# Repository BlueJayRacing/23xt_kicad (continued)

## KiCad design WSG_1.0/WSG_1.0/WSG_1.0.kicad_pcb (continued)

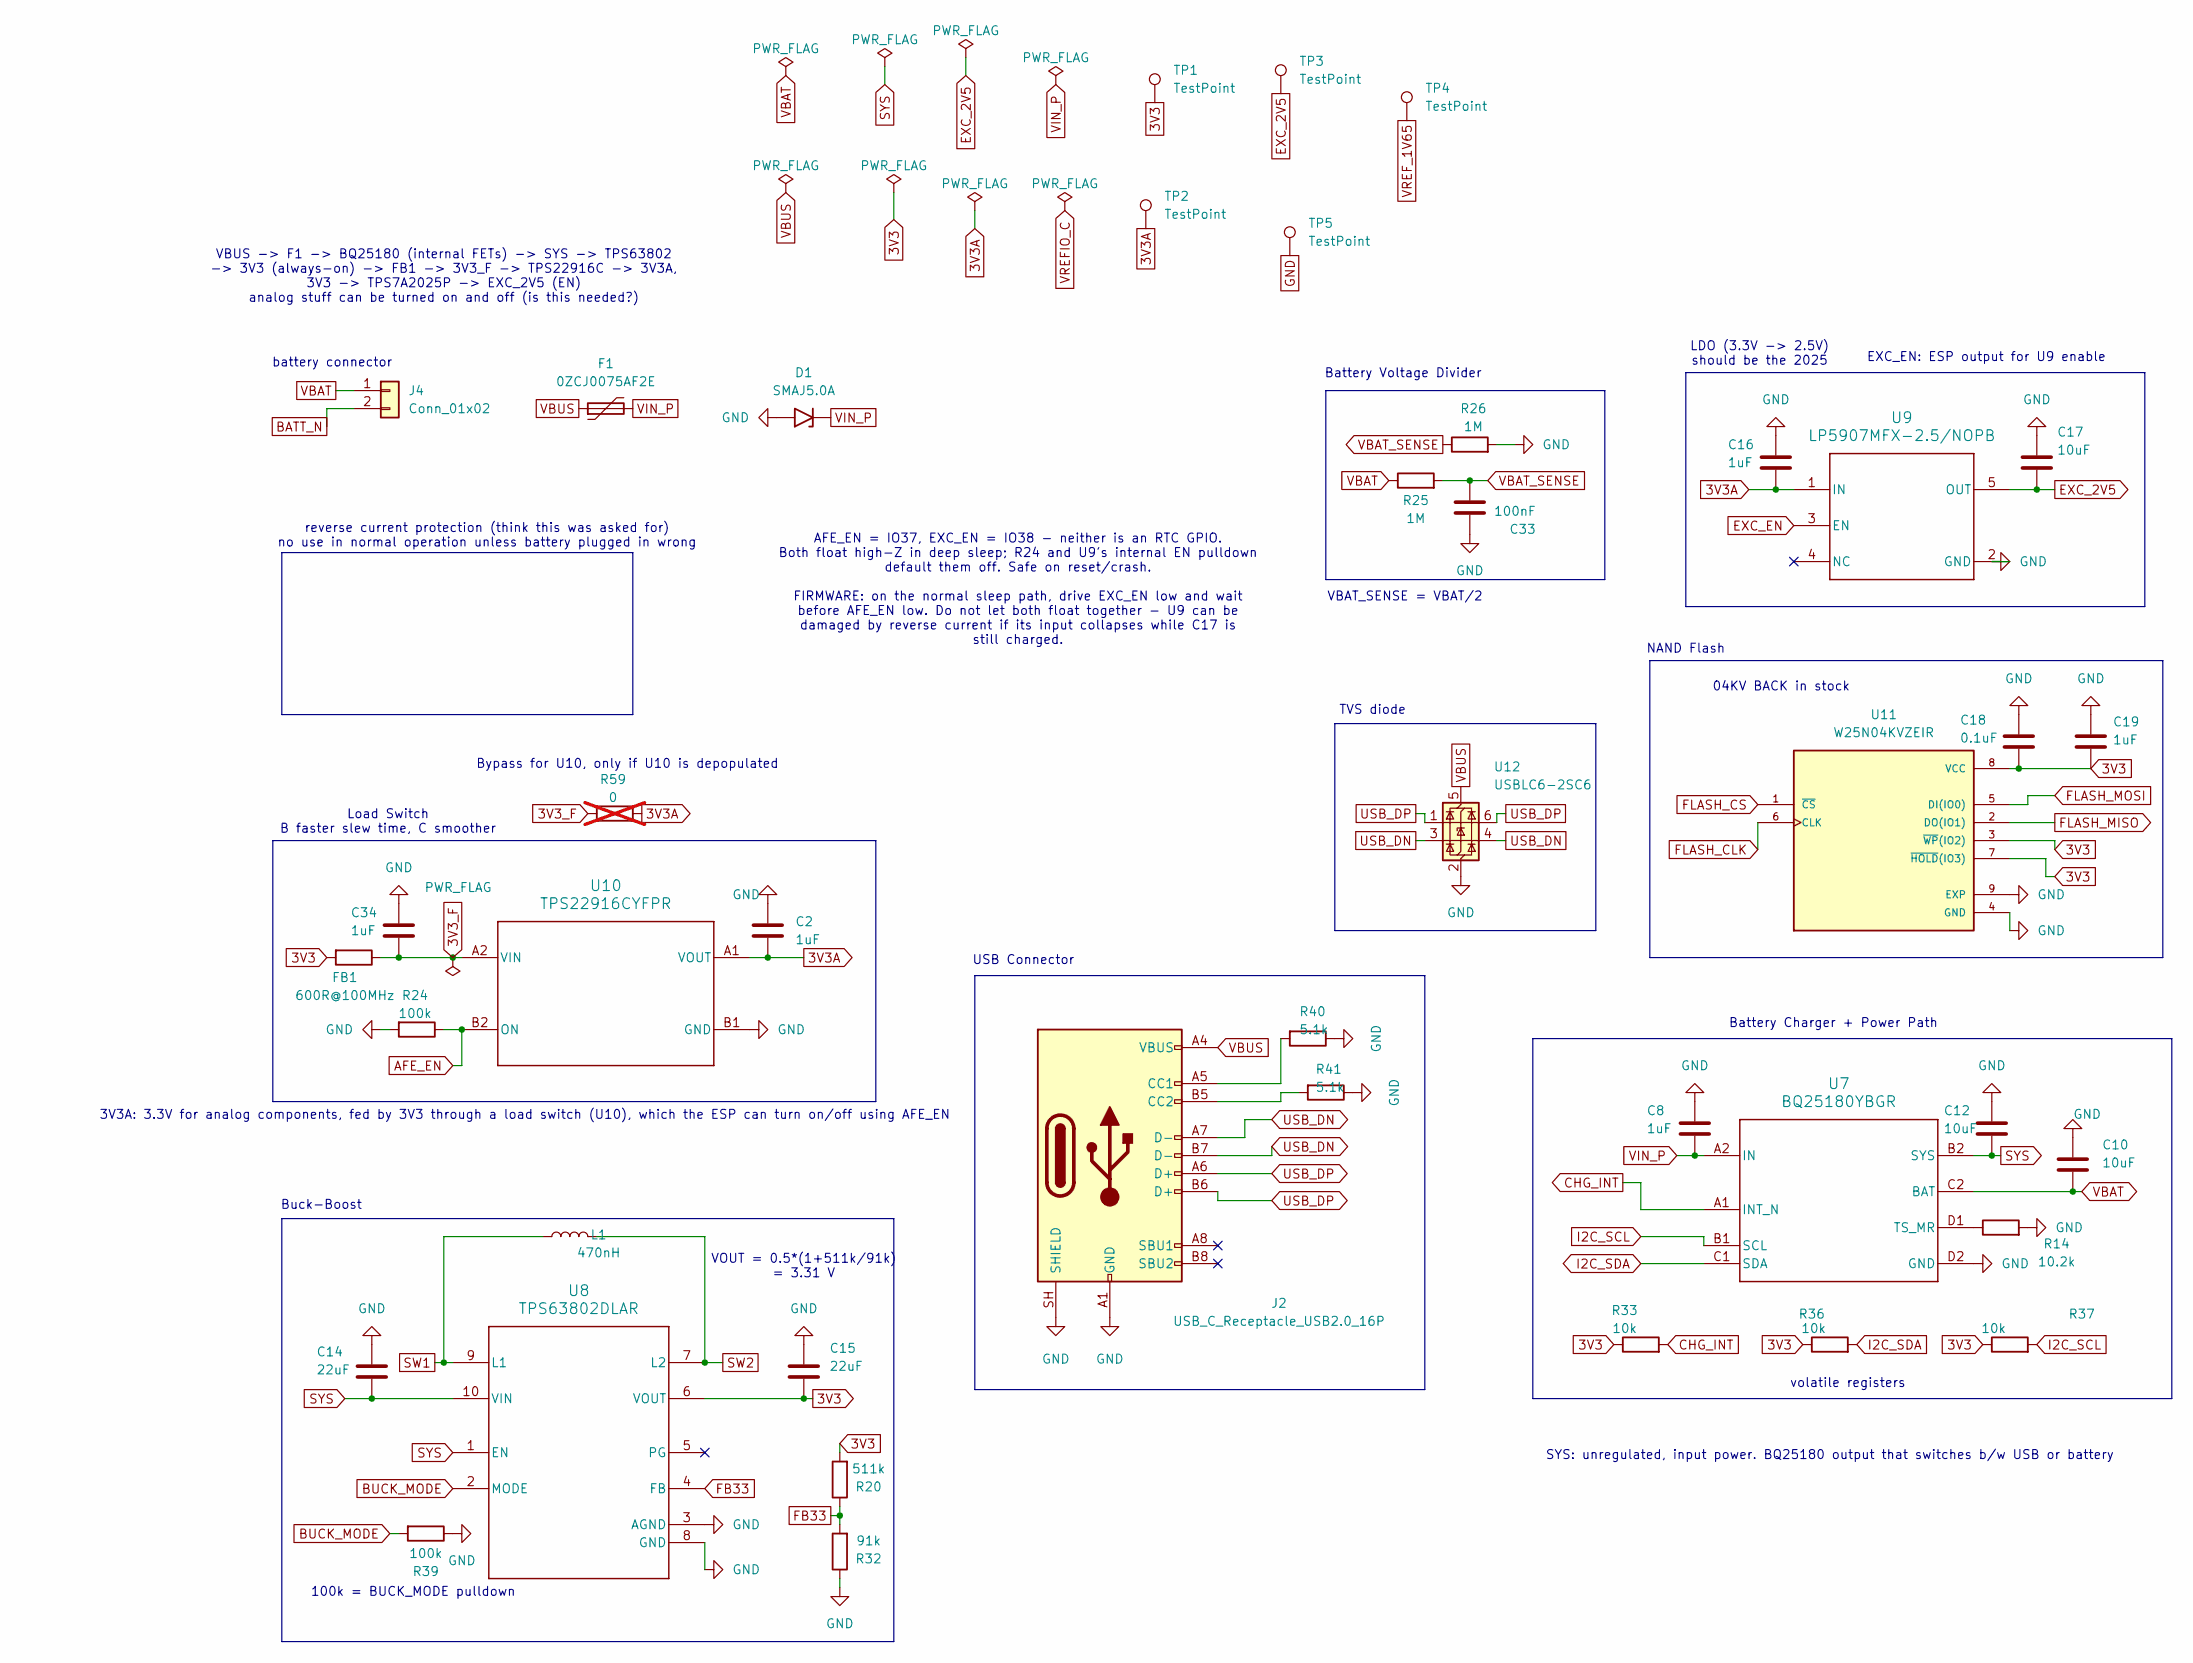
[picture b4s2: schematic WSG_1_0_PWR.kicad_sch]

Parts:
C2, C8, C16, C19, C34: 1uF; C_0402_1005Metric_Pad0.74x0.62mm_HandSolder
C10, C12: 10uF; C_0402_1005Metric_Pad0.74x0.62mm_HandSolder
C14, C15: 22uF; C_0603_1608Metric_Pad1.08x0.95mm_HandSolder; MPN CL10A226MQ8NRNE
C17: 10uF; C_0603_1608Metric_Pad1.08x0.95mm_HandSolder; MPN GRM188R60J106ME84
C18: 0.1uF; C_0402_1005Metric_Pad0.74x0.62mm_HandSolder
C33: 100nF; C_0402_1005Metric_Pad0.74x0.62mm_HandSolder
D1: SMAJ5.0A; D_SMA
F1: 0ZCJ0075AF2E; Fuse_1206_3216Metric
FB1: 600R@100MHz; L_0402_1005Metric; MPN BLM15AG601SN1D
J2: USB_C_Receptacle_USB2.0_16P; USB_C_Receptacle_GCT_USB4110; MPN USB4110-GF-A
J4: Conn_01x02; JST_S2B-PH-K-S_LF__SN_-2pin_male
L1: 470nH; L_Coilcraft_XxL4020; MPN XGL4020-471MEC
R14: 10.2k; R_0402_1005Metric_Pad0.72x0.64mm_HandSolder
R20: 511k; R_0402_1005Metric_Pad0.72x0.64mm_HandSolder
R24, R39: 100k; R_0402_1005Metric_Pad0.72x0.64mm_HandSolder
R25, R26: 1M; R_0402_1005Metric_Pad0.72x0.64mm_HandSolder
R32: 91k; R_0402_1005Metric_Pad0.72x0.64mm_HandSolder
R33, R36, R37: 10k; R_0402_1005Metric_Pad0.72x0.64mm_HandSolder
R40, R41: 5.1k; R_0402_1005Metric_Pad0.72x0.64mm_HandSolder
R59: 0; R_0402_1005Metric_Pad0.72x0.64mm_HandSolder; not fitted
TP1, TP2, TP3, TP4, TP5: TestPoint; TestPoint_Pad_1.0x1.0mm
U7: BQ25180YBGR; IC_BQ25180YBGR
U8: TPS63802DLAR; DLA0010A
U9: LP5907MFX-2.5/NOPB; SOT-23-5
U10: TPS22916CYFPR; IC_TPS22916BYFPR
U11: W25N04KVZEIR; IC_W25N04KVZEIR; PARTREV I
U12: USBLC6-2SC6; SOT-23-6

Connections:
3V3: C15.2, C18.2, C19.2, FB1.2, R20.2, R33.1, R36.1, R37.1, TP1.1 (1_1), U8.6 (VOUT), U11.3 (~WP(IO2)), U11.7 (~HOLD(IO3)), U11.8 (VCC); also elsewhere on the board
3V3A: C2.2, C16.2, R59.1, TP2.1 (1_1), U9.1 (IN), U10.A1 (VOUT); also elsewhere on the board
3V3_F: C34.2, FB1.1, R59.2, U10.A2 (VIN)
AFE_EN: R24.1, U10.B2 (ON); also elsewhere on the board
BATT_N: J4.2; also elsewhere on the board
BUCK_MODE: R39.2, U8.2 (MODE); also elsewhere on the board
CHG_INT: R33.2, U7.A1 (INT_N); also elsewhere on the board
EXC_2V5: C17.2, TP3.1 (1_1), U9.5 (OUT); also elsewhere on the board
EXC_EN: U9.3 (EN); also elsewhere on the board
FB33: R20.1, R32.2, U8.4 (FB)
FLASH_CLK: U11.6 (CLK); also elsewhere on the board
FLASH_CS: U11.1 (~CS); also elsewhere on the board
FLASH_MISO: U11.2 (DO(IO1)); also elsewhere on the board
FLASH_MOSI: U11.5 (DI(IO0)); also elsewhere on the board
GND: C2.1, C8.1, C10.1, C12.1, C14.1, C15.1, C16.1, C17.1, C18.1, C19.1, C33.2, C34.1, D1.2 (A2), J2.A1 (GND), J2.A12 (GND), J2.B1 (GND), J2.B12 (GND), J2.SH (SHIELD), R14.2, R24.2, R26.2, R32.1, R39.1, R40.1, R41.1, TP5.1 (1_1), U7.D2 (GND), U8.3 (AGND), U8.8 (GND), U9.2 (GND), U10.B1 (GND), U11.4 (GND), U11.9 (EXP), U12.2 (GND); also elsewhere on the board
I2C_SCL: R37.2, U7.B1 (SCL); also elsewhere on the board
I2C_SDA: R36.2, U7.C1 (SDA); also elsewhere on the board
unnamed: J2.A5 (CC1), R40.2
unnamed: J2.B5 (CC2), R41.2
unnamed: R14.1, U7.D1 (TS_MR)
SW1: L1.1, U8.9 (L1)
SW2: L1.2, U8.7 (L2)
SYS: C12.2, C14.2, U7.B2 (SYS), U8.1 (EN), U8.10 (VIN)
USB_DN: J2.A7 (D-), J2.B7 (D-), U12.3 (I/O2), U12.4 (I/O2); also elsewhere on the board
USB_DP: J2.A6 (D+), J2.B6 (D+), U12.1 (I/O1), U12.6 (I/O1); also elsewhere on the board
VBAT: C10.2, J4.1, R25.1, U7.C2 (BAT)
VBAT_SENSE: C33.1, R25.2, R26.1; also elsewhere on the board
VBUS: F1.1, J2.A4 (VBUS), J2.A9 (VBUS), J2.B4 (VBUS), J2.B9 (VBUS), U12.5 (VBUS)
VIN_P: C8.2, D1.1 (A1), F1.2, U7.A2 (IN)
VREF_1V65: TP4.1 (1_1); also elsewhere on the board

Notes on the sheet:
3V3A: 3.3V for analog components, fed by 3V3 through a load switch (U10), which the ESP can turn on/off using AFE_EN
100k = BUCK_MODE pulldown
LDO (3.3V -> 2.5V) should be the 2025
04KV BACK in stock
Battery Voltage Divider
NAND Flash
VBAT_SENSE = VBAT/2
volatile registers
EXC_EN: ESP output for U9 enable
Load Switch B faster slew time, C smoother
Battery Charger + Power Path
VBUS -> F1 -> BQ25180 (internal FETs) -> SYS -> TPS63802 -> 3V3 (always-on) -> FB1 -> 3V3_F -> TPS22916C -> 3V3A, 3V3 -> TPS7A2025P -> EXC_2V5 (EN) analog stuff can be turned on and off (is this needed?)
AFE_EN = IO37, EXC_EN = IO38 - neither is an RTC GPIO. Both float high-Z in deep sleep; R24 and U9's internal EN pulldown default them off. Safe on reset/crash. FIRMWARE: on the normal sleep path, drive EXC_EN low and wait before AFE_EN low. Do not let both float together - U9 can be damaged by rev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
Buck-Boost
USB Connector
battery connector
reverse current protection (think this was asked for) no use in normal operation unless battery plugged in wrong
SYS: unregulated, input power. BQ25180 output that switches b/w USB or battery
TVS diode
Bypass for U10, only if U10 is depopulated
VOUT = 0.5*(1+511k/91k) = 3.31 V

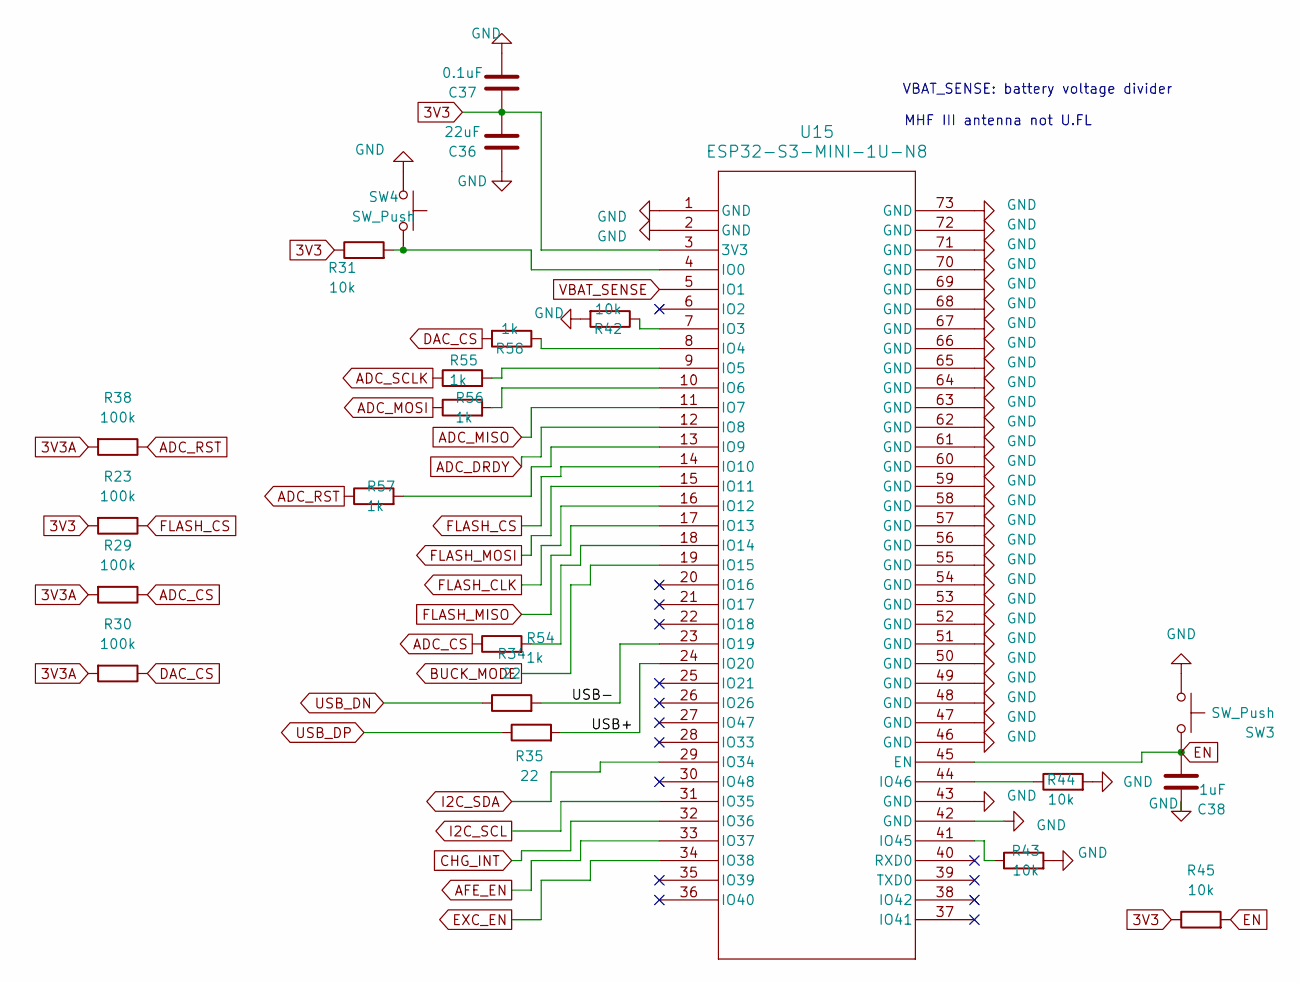
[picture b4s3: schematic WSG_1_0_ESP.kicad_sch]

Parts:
C36: 22uF; C_0603_1608Metric_Pad1.08x0.95mm_HandSolder; MPN CL10A226MQ8NRNE
C37: 0.1uF; C_0402_1005Metric_Pad0.74x0.62mm_HandSolder
C38: 1uF; C_0402_1005Metric_Pad0.74x0.62mm_HandSolder
R23, R29, R30, R38: 100k; R_0402_1005Metric_Pad0.72x0.64mm_HandSolder
R31, R42, R43, R44, R45: 10k; R_0402_1005Metric_Pad0.72x0.64mm_HandSolder
R34, R35: 22; R_0402_1005Metric_Pad0.72x0.64mm_HandSolder
R54, R55, R56, R57, R58: 1k; R_0402_1005Metric_Pad0.72x0.64mm_HandSolder
SW3, SW4: SW_Push; NANOT100AS_butt
U15: ESP32-S3-MINI-1U-N8; ESP32-S3-MINI-1U_EXP

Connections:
3V3: C36.1, C37.1, R23.2, R31.1, R45.1, U15.3 (3V3); also elsewhere on the board
3V3A: R29.2, R30.2, R38.2; also elsewhere on the board
/WSG_ESP/USB+: R35.2, U15.24 (IO20)
/WSG_ESP/USB-: R34.2, U15.23 (IO19)
ADC_CS: R29.1, R54.1; also elsewhere on the board
ADC_DRDY: U15.12 (IO8); also elsewhere on the board
ADC_MISO: U15.11 (IO7); also elsewhere on the board
ADC_MOSI: R56.1; also elsewhere on the board
ADC_RST: R38.1, R57.1; also elsewhere on the board
ADC_SCLK: R55.1; also elsewhere on the board
AFE_EN: U15.33 (IO37); also elsewhere on the board
BUCK_MODE: U15.19 (IO15); also elsewhere on the board
CHG_INT: U15.32 (IO36); also elsewhere on the board
DAC_CS: R30.1, R58.2; also elsewhere on the board
EN: C38.2, R45.2, SW3.2, U15.45 (EN)
EXC_EN: U15.34 (IO38); also elsewhere on the board
FLASH_CLK: U15.16 (IO12); also elsewhere on the board
FLASH_CS: R23.1, U15.14 (IO10); also elsewhere on the board
FLASH_MISO: U15.17 (IO13); also elsewhere on the board
FLASH_MOSI: U15.15 (IO11); also elsewhere on the board
GND: C36.2, C37.2, C38.1, R42.2, R43.2, R44.2, SW3.1, SW4.1, U15.1 (GND), U15.2 (GND), U15.42 (GND), U15.43 (GND), U15.46 (GND), U15.47 (GND), U15.48 (GND), U15.49 (GND), U15.50 (GND), U15.51 (GND), U15.52 (GND), U15.53 (GND), U15.54 (GND), U15.55 (GND), U15.56 (GND), U15.57 (GND), U15.58 (GND), U15.59 (GND), U15.60 (GND), U15.61 (GND), U15.62 (GND), U15.63 (GND), U15.64 (GND), U15.65 (GND), U15.66 (GND), U15.67 (GND), U15.68 (GND), U15.69 (GND), U15.70 (GND), U15.71 (GND), U15.72 (GND), U15.73 (GND); also elsewhere on the board
I2C_SCL: U15.31 (IO35); also elsewhere on the board
I2C_SDA: U15.29 (IO34); also elsewhere on the board
unnamed: R31.2, SW4.2, U15.4 (IO0)
unnamed: R42.1, U15.7 (IO3)
unnamed: R58.1, U15.8 (IO4)
unnamed: R55.2, U15.9 (IO5)
unnamed: R56.2, U15.10 (IO6)
unnamed: R57.2, U15.13 (IO9)
unnamed: R54.2, U15.18 (IO14)
unnamed: R43.1, U15.41 (IO45)
unnamed: R44.1, U15.44 (IO46)
USB_DN: R34.1; also elsewhere on the board
USB_DP: R35.1; also elsewhere on the board
VBAT_SENSE: U15.5 (IO1); also elsewhere on the board

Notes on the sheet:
MHF III antenna not U.FL
VBAT_SENSE: battery voltage divider

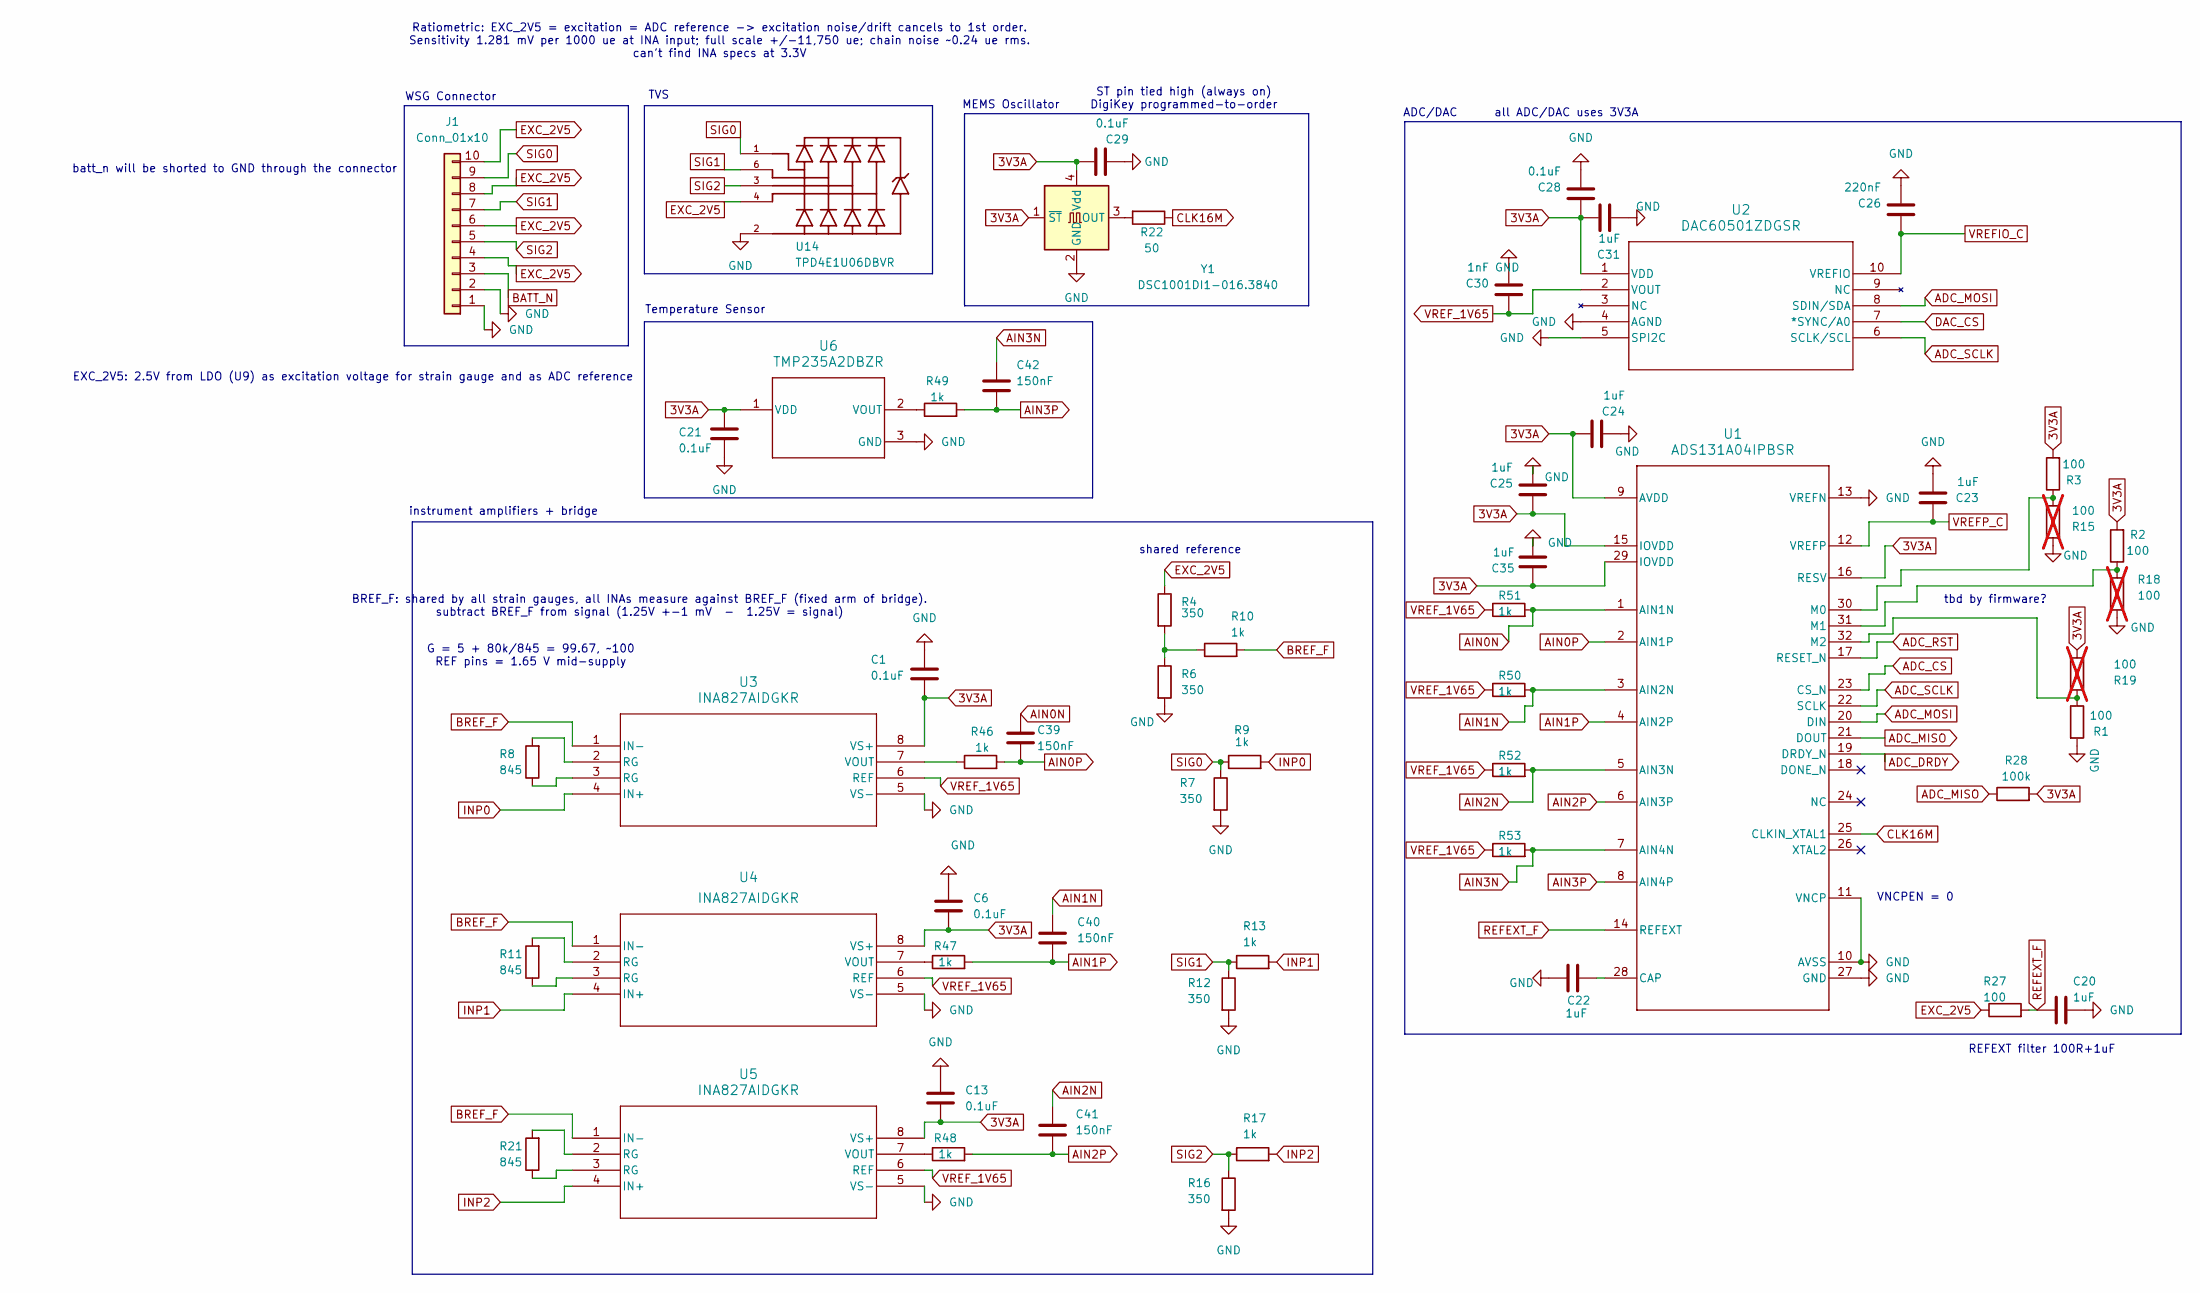
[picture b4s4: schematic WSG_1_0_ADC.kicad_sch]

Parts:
C1, C6, C13, C21, C28, C29: 0.1uF; C_0402_1005Metric_Pad0.74x0.62mm_HandSolder
C20, C22, C23, C24, C25, C31, C35: 1uF; C_0402_1005Metric_Pad0.74x0.62mm_HandSolder
C26: 220nF; C_0402_1005Metric_Pad0.74x0.62mm_HandSolder
C30: 1nF; C_0402_1005Metric_Pad0.74x0.62mm_HandSolder
C39, C40, C41, C42: 150nF; C_0402_1005Metric_Pad0.74x0.62mm_HandSolder
J1: Conn_01x10; PinHeader_2x05_P2.00mm_Vertical
R1, R2, R3, R27: 100; R_0402_1005Metric_Pad0.72x0.64mm_HandSolder
R4, R6, R7, R12, R16: 350; R_0402_1005Metric_Pad0.72x0.64mm_HandSolder
R8, R11, R21: 845; R_0402_1005Metric_Pad0.72x0.64mm_HandSolder
R9, R10, R13, R17, R46, R47, R48, R49, R50, R51, R52, R53: 1k; R_0402_1005Metric_Pad0.72x0.64mm_HandSolder
R15, R18, R19: 100; R_0402_1005Metric_Pad0.72x0.64mm_HandSolder; not fitted
R22: 50; R_0402_1005Metric_Pad0.72x0.64mm_HandSolder
R28: 100k; R_0402_1005Metric_Pad0.72x0.64mm_HandSolder
U1: ADS131A04IPBSR; TQFP-32_5x5mm_P0.5mm
U2: DAC60501ZDGSR; MSOP-10_3x3mm_P0.5mm
U3, U4, U5: INA827AIDGKR; VSSOP-8_3x3mm_P0.65mm
U6: TMP235A2DBZR; SOT-23
U14: TPD4E1U06DBVR; SOT95P280X145-6N; PARTREV D
Y1: DSC1001DI1-016.3840; Oscillator_SMD_SiT_PQFN-4Pin_2.5x2.0mm

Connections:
3V3A: C1.1, C6.1, C13.1, C21.1, C24.2, C25.2, C28.2, C29.2, C31.2, C35.2, R2.2, R3.2, R19.1, R28.2, U1.9 (AVDD), U1.15 (IOVDD), U1.16 (RESV), U1.29 (IOVDD), U2.1 (VDD), U3.8 (VS+), U4.8 (VS+), U5.8 (VS+), U6.1 (VDD), Y1.1 (~ST), Y1.4 (Vdd); also elsewhere on the board
ADC_CS: U1.23 (CS_N); also elsewhere on the board
ADC_DRDY: U1.19 (DRDY_N); also elsewhere on the board
ADC_MISO: R28.1, U1.21 (DOUT); also elsewhere on the board
ADC_MOSI: U1.20 (DIN), U2.8 (SDIN/SDA); also elsewhere on the board
ADC_RST: U1.17 (RESET_N); also elsewhere on the board
ADC_SCLK: U1.22 (SCLK), U2.6 (SCLK/SCL); also elsewhere on the board
AIN0N: C39.2, R51.2, U1.1 (AIN1N)
AIN0P: C39.1, R46.2, U1.2 (AIN1P)
AIN1N: C40.2, R50.2, U1.3 (AIN2N)
AIN1P: C40.1, R47.2, U1.4 (AIN2P)
AIN2N: C41.2, R52.2, U1.5 (AIN3N)
AIN2P: C41.1, R48.2, U1.6 (AIN3P)
AIN3N: C42.2, R53.2, U1.7 (AIN4N)
AIN3P: C42.1, R49.2, U1.8 (AIN4P)
BATT_N: J1.3; also elsewhere on the board
BREF_F: R10.2, U3.1 (IN-), U4.1 (IN-), U5.1 (IN-)
CLK16M: R22.1, U1.25 (CLKIN_XTAL1)
DAC_CS: U2.7 (*SYNC/A0); also elsewhere on the board
EXC_2V5: J1.4, J1.6, J1.8, J1.10, R4.1, R27.1, U14.4; also elsewhere on the board
GND: C1.2, C6.2, C13.2, C20.2, C21.2, C22.1, C23.1, C24.1, C25.1, C26.1, C28.1, C29.1, C30.1, C31.1, C35.1, J1.1, J1.2, R1.2, R6.2, R7.2, R12.2, R15.1, R16.2, R18.1, U1.10 (AVSS), U1.11 (VNCP), U1.13 (VREFN), U1.27 (GND), U2.4 (AGND), U2.5 (SPI2C), U3.5 (VS-), U4.5 (VS-), U5.5 (VS-), U6.3 (GND), U14.2, Y1.2 (GND); also elsewhere on the board
INP0: R9.2, U3.4 (IN+)
INP1: R13.2, U4.4 (IN+)
INP2: R17.2, U5.4 (IN+)
unnamed: R8.1, U3.3 (RG)
unnamed: R8.2, U3.2 (RG)
unnamed: R4.2, R6.1, R10.1
unnamed: R11.1, U4.3 (RG)
unnamed: R11.2, U4.2 (RG)
unnamed: R21.1, U5.3 (RG)
unnamed: R21.2, U5.2 (RG)
unnamed: C22.2, U1.28 (CAP)
unnamed: R3.1, R15.2, U1.30 (M0)
unnamed: R2.1, R18.2, U1.31 (M1)
unnamed: R1.1, R19.2, U1.32 (M2)
unnamed: R46.1, U3.7 (VOUT)
unnamed: R47.1, U4.7 (VOUT)
unnamed: R48.1, U5.7 (VOUT)
unnamed: R49.1, U6.2 (VOUT)
unnamed: R22.2, Y1.3 (OUT)
REFEXT_F: C20.1, R27.2, U1.14 (REFEXT)
SIG0: J1.9, R7.1, R9.1, U14.1
SIG1: J1.7, R12.1, R13.1, U14.6
SIG2: J1.5, R16.1, R17.1, U14.3
VREFIO_C: C26.2, U2.10 (VREFIO)
VREFP_C: C23.2, U1.12 (VREFP)
VREF_1V65: C30.2, R50.1, R51.1, R52.1, R53.1, U2.2 (VOUT), U3.6 (REF), U4.6 (REF), U5.6 (REF); also elsewhere on the board

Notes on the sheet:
batt_n will be shorted to GND through the connector
Ratiometric: EXC_2V5 = excitation = ADC reference -> excitation noise/drift cancels to 1st order. Sensitivity 1.281 mV per 1000 ue at INA input; full scale +/-11,750 ue; chain noise ~0.24 ue rms. can't find INA specs at 3.3V
instrument amplifiers + bridge
BREF_F: shared by all strain gauges, all INAs measure against BREF_F (fixed arm of bridge). subtract BREF_F from signal (1.25V +-1 mV - 1.25V = signal)
shared reference
EXC_2V5: 2.5V from LDO (U9) as excitation voltage for strain gauge and as ADC reference
ADC/DAC
all ADC/DAC uses 3V3A
REFEXT filter 100R+1uF
G = 5 + 80k/845 = 99.67, ~100 REF pins = 1.65 V mid-supply
MEMS Oscillator
Temperature Sensor
WSG Connector
TVS
tbd by firmware?
VNCPEN = 0
ST pin tied high (always on) DigiKey programmed-to-order

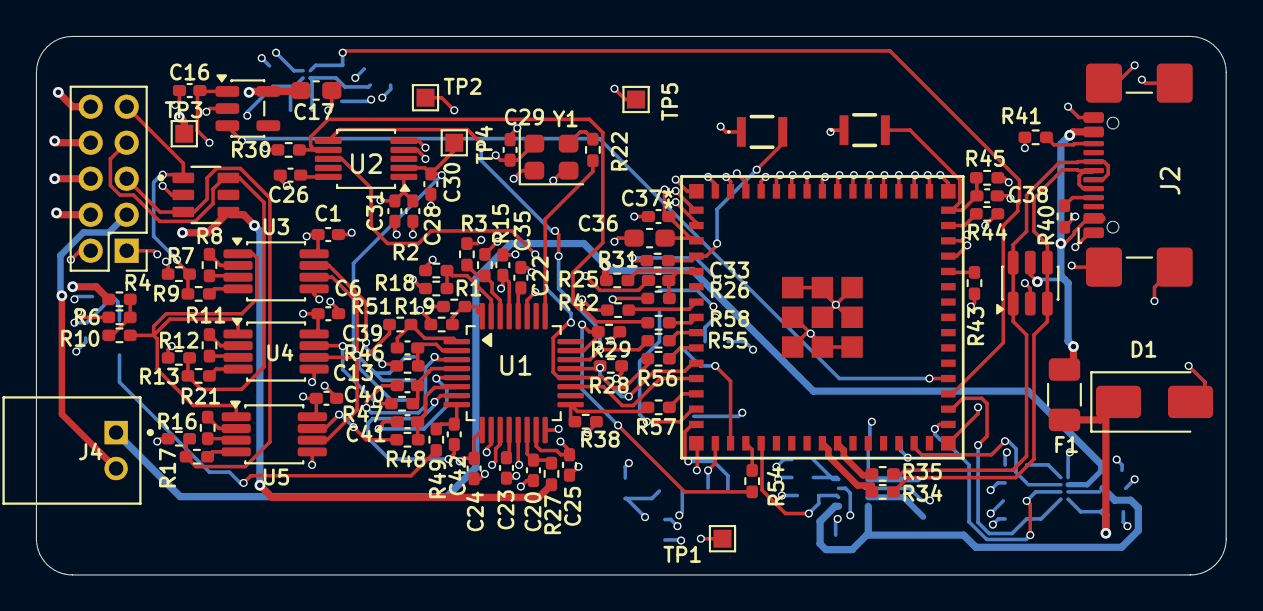
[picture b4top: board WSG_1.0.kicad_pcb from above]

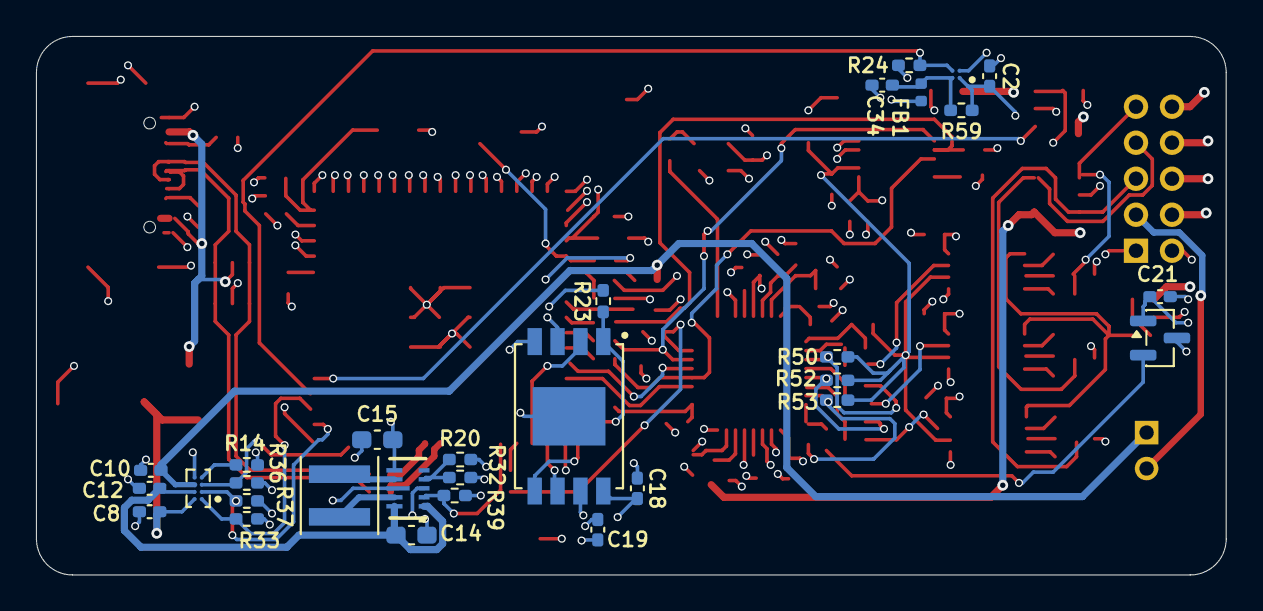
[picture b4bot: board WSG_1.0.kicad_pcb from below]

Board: 4 copper layers, 66.1 x 29.9 mm, 121 parts (30 on the bottom side), 84 nets.

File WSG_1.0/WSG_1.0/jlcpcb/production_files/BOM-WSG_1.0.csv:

Comment,Designator,Footprint,LCSC,Quantity
0.1uF,"C1,C13,C18,C21,C28,C29,C37,C6",C_0402_1005Metric_Pad0.74x0.62mm_HandSolder,C1525,8
0ZCJ0075AF2E,F1,Fuse_1206_3216Metric,C3761319,1
10.2k,R14,R_0402_1005Metric_Pad0.72x0.64mm_HandSolder,C11660,1
100,"R1,R2,R27,R3",R_0402_1005Metric_Pad0.72x0.64mm_HandSolder,C25076,4
100k,"R23,R24,R28,R29,R30,R38,R39",R_0402_1005Metric_Pad0.72x0.64mm_HandSolder,C25741,7
100nF,C33,C_0402_1005Metric_Pad0.74x0.62mm_HandSolder,C1525,1
10k,"R31,R33,R36,R37,R42,R43,R44,R45",R_0402_1005Metric_Pad0.72x0.64mm_HandSolder,C25744,8
10uF,"C10,C12",C_0402_1005Metric_Pad0.74x0.62mm_HandSolder,C15525,2
10uF,C17,C_0603_1608Metric_Pad1.08x0.95mm_HandSolder,C19702,1
150nF,"C39,C40,C41,C42",C_0402_1005Metric_Pad0.74x0.62mm_HandSolder,C162182,4
1M,"R25,R26",R_0402_1005Metric_Pad0.72x0.64mm_HandSolder,C26083,2
1k,"R10,R13,R17,R46,R47,R48,R49,R50,R51,R52,R53,R54,R55,R56,R57,R58,R9",R_0402_1005Metric_Pad0.72x0.64mm_HandSolder,C11702,17
1nF,C30,C_0402_1005Metric_Pad0.74x0.62mm_HandSolder,C1523,1
1uF,"C16,C19,C2,C20,C22,C23,C24,C25,C31,C34,C35,C38,C8",C_0402_1005Metric_Pad0.74x0.62mm_HandSolder,C52923,13
22,"R34,R35",R_0402_1005Metric_Pad0.72x0.64mm_HandSolder,C25092,2
220nF,C26,C_0402_1005Metric_Pad0.74x0.62mm_HandSolder,C16772,1
22uF,"C14,C15,C36",C_0603_1608Metric_Pad1.08x0.95mm_HandSolder,C59461,3
350,"R12,R16,R4,R6,R7",R_0402_1005Metric_Pad0.72x0.64mm_HandSolder,C852731,5
470nH,L1,L_Coilcraft_XxL4020,C5837785,1
5.1k,"R40,R41",R_0402_1005Metric_Pad0.72x0.64mm_HandSolder,C25905,2
50,R22,R_0402_1005Metric_Pad0.72x0.64mm_HandSolder,C25120,1
511k,R20,R_0402_1005Metric_Pad0.72x0.64mm_HandSolder,C64042,1
600R@100MHz,FB1,L_0402_1005Metric,C76884,1
845,"R11,R21,R8",R_0402_1005Metric_Pad0.72x0.64mm_HandSolder,C852931,3
91k,R32,R_0402_1005Metric_Pad0.72x0.64mm_HandSolder,C4147,1
ADS131A04IPBSR,U1,TQFP-32_5x5mm_P0.5mm,C2861481,1
BQ25180YBGR,U7,IC_BQ25180YBGR,C3682423,1
DAC60501ZDGSR,U2,MSOP-10_3x3mm_P0.5mm,C1852027,1
DSC1001DI1-016.3840,Y1,Oscillator_SMD_SiT_PQFN-4Pin_2.5x2.0mm,C1670360,1
ESP32-S3-MINI-1U-N8,U15,ESP32-S3-MINI-1U_EXP,C2980299,1
INA827AIDGKR,"U3,U4,U5",VSSOP-8_3x3mm_P0.65mm,C2860185,3
LP5907MFX-2.5/NOPB,U9,SOT-23-5,C165132,1
SMAJ5.0A,D1,D_SMA,C10758,1
SW_Push,"SW3,SW4",NANOT100AS_butt,C2760981,2
TMP235A2DBZR,U6,SOT-23,C2868808,1
TPD4E1U06DBVR,U14,SOT95P280X145-6N,C124691,1
TPS22916CYFPR,U10,IC_TPS22916BYFPR,C2680319,1
TPS63802DLAR,U8,DLA0010A,C2845237,1
USBLC6-2SC6,U12,SOT-23-6,C7519,1
USB_C_Receptacle_USB2.0_16P,J2,USB_C_Receptacle_GCT_USB4110,C5143397,1
W25N04KVZEIR,U11,IC_W25N04KVZEIR,C5342170,1
Conn_01x10,J1,PinHeader_2x05_P2.00mm_Vertical,,1
Conn_01x02,J4,JST_S2B-PH-K-S_LF__SN_-2pin_male,,1

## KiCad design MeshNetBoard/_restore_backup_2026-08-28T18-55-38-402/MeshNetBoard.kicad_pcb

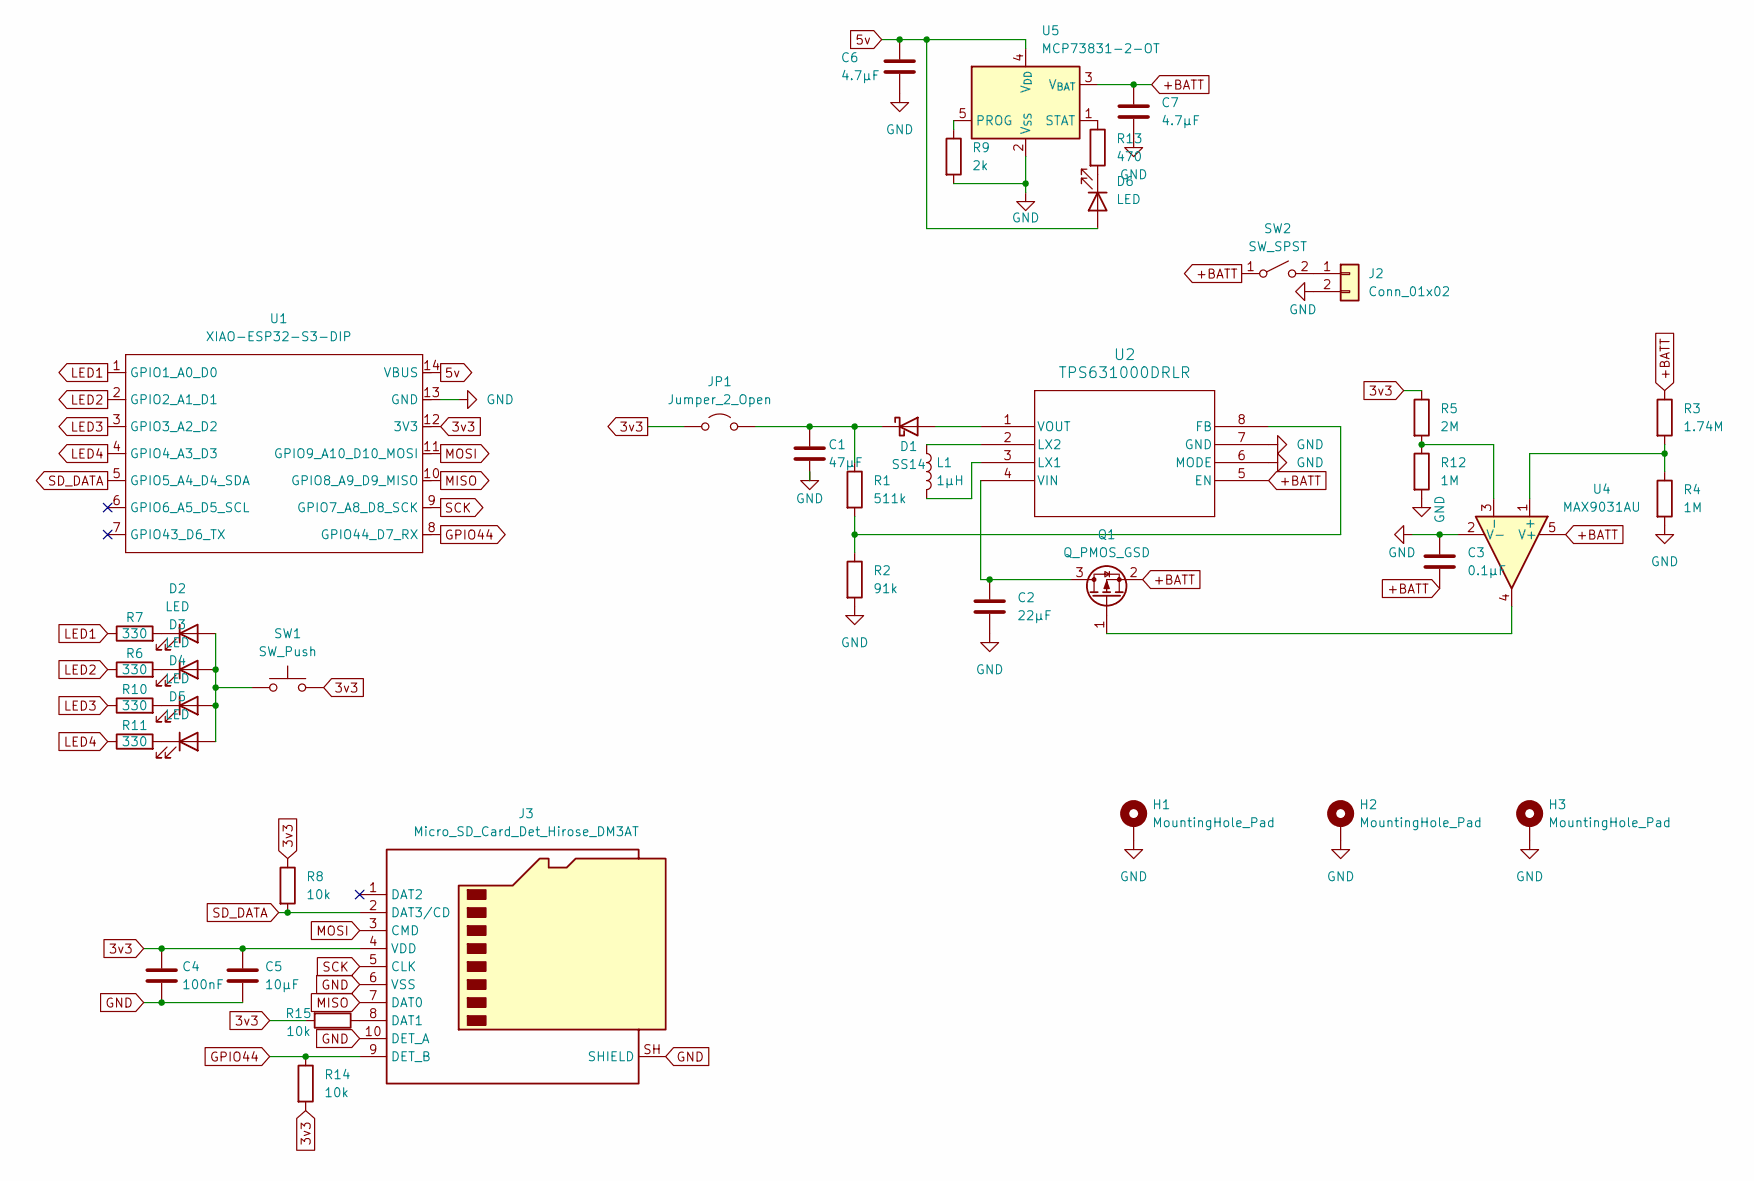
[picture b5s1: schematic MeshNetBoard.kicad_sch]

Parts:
C1: 47µF; C_0603_1608Metric_Pad1.08x0.95mm_HandSolder
C2: 22µF; C_0603_1608Metric_Pad1.08x0.95mm_HandSolder
C3: 0.1μF; C_0603_1608Metric_Pad1.08x0.95mm_HandSolder
C4: 100nF; C_0603_1608Metric_Pad1.08x0.95mm_HandSolder
C5: 10µF; C_0603_1608Metric_Pad1.08x0.95mm_HandSolder
C6, C7: 4.7µF; C_0603_1608Metric_Pad1.08x0.95mm_HandSolder
D1: SS14; D_SMA
D2, D3, D4, D5, D6: LED; LED_1206_3216Metric_Pad1.42x1.75mm_HandSolder
H1, H2, H3: MountingHole_Pad; MountingHole_2.2mm_M2_Pad_TopBottom
J2: Conn_01x02; JST_PH_S2B-PH-K_1x02_P2.00mm_Horizontal
J3: Micro_SD_Card_Det_Hirose_DM3AT; microSD_HC_Hirose_DM3AT-SF-PEJM5
JP1: Jumper_2_Open; PinSocket_1x02_P2.54mm_Vertical
L1: 1µH; L_0603_1608Metric_Pad1.05x0.95mm_HandSolder
Q1: Q_PMOS_GSD; SOT-23
R1: 511k; R_0603_1608Metric_Pad0.98x0.95mm_HandSolder
R2: 91k; R_0603_1608Metric_Pad0.98x0.95mm_HandSolder
R3: 1.74M; R_0603_1608Metric_Pad0.98x0.95mm_HandSolder
R4, R12: 1M; R_0603_1608Metric_Pad0.98x0.95mm_HandSolder
R5: 2M; R_0603_1608Metric_Pad0.98x0.95mm_HandSolder
R6, R7, R10, R11: 330; R_0603_1608Metric_Pad0.98x0.95mm_HandSolder
R8, R14, R15: 10k; R_0603_1608Metric_Pad0.98x0.95mm_HandSolder
R9: 2k; R_0603_1608Metric_Pad0.98x0.95mm_HandSolder
R13: 470; R_0603_1608Metric_Pad0.98x0.95mm_HandSolder
SW1: SW_Push; SW_PUSH_6mm_H5mm
SW2: SW_SPST; SW_Slide_SPDT_Angled_CK_OS102011MA1Q
U1: XIAO-ESP32-S3-DIP
U2: TPS631000DRLR; TPS631000DRLR_TEX
U4: MAX9031AU; SOT-23-5
U5: MCP73831-2-OT; SOT-23-5

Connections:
3v3: C4.1, C5.1, J3.4 (VDD), JP1.1 (A), R5.1, R8.1, R14.2, R15.2, SW1.2, U1.12 (3V3)
5v: C6.1, D6.2 (A), U1.14 (VBUS), U5.4 (V_{DD})
+BATT: C3.2, C7.1, Q1.2 (S), R3.1, SW2.1 (A), U2.5 (EN), U4.5 (V+), U5.3 (V_{BAT})
GND: C1.2, C2.2, C3.1, C4.2, C5.2, C6.2, C7.2, H1.1 (1_1), H2.1 (1_1), H3.1 (1_1), J2.2, J3.6 (VSS), J3.10 (DET_A), J3.SH (SHIELD), R2.2, R4.2, R9.2, R12.2, U1.13 (GND), U2.6 (MODE), U2.7 (GND), U4.2 (V-), U5.2 (V_{SS})
GPIO44: J3.9 (DET_B), R14.1, U1.8 (GPIO44_D7_RX)
LED1: R7.1, U1.1 (GPIO1_A0_D0)
LED2: R6.1, U1.2 (GPIO2_A1_D1)
LED3: R10.1, U1.3 (GPIO3_A2_D2)
LED4: R11.1, U1.4 (GPIO4_A3_D3)
MISO: J3.7 (DAT0), U1.10 (GPIO8_A9_D9_MISO)
MOSI: J3.3 (CMD), U1.11 (GPIO9_A10_D10_MOSI)
unnamed: D1.2 (A), U2.1 (VOUT)
unnamed: C1.1, D1.1 (K), JP1.2 (B), R1.1
unnamed: D2.2 (A), D3.2 (A), D4.2 (A), D5.2 (A), SW1.1
unnamed: D2.1 (K), R7.2
unnamed: D3.1 (K), R6.2
unnamed: D4.1 (K), R10.2
unnamed: D5.1 (K), R11.2
unnamed: D6.1 (K), R13.2
unnamed: J2.1, SW2.2 (B)
unnamed: J3.8 (DAT1), R15.1
unnamed: C2.1, Q1.3 (D), U2.4 (VIN)
unnamed: Q1.1 (G), U4.4
unnamed: R1.2, R2.1, U2.8 (FB)
unnamed: L1.2, U2.3 (LX1)
unnamed: L1.1, U2.2 (LX2)
unnamed: R3.2, R4.1, U4.1 (+)
unnamed: R5.2, R12.1, U4.3 (-)
unnamed: R9.1, U5.5 (PROG)
unnamed: R13.1, U5.1 (STAT)
SCK: J3.5 (CLK), U1.9 (GPIO7_A8_D8_SCK)
SD_DATA: J3.2 (DAT3/CD), R8.2, U1.5 (GPIO5_A4_D4_SDA)
